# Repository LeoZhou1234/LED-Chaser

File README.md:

# LED Chaser #
Made by following the tutorial from Hack Club Blueprint.  
Gerbers were generated matching JLCPCB guidelines.

## Schematic ##

## PCB ##

(Snoopy silkscreen omitted for clarity)

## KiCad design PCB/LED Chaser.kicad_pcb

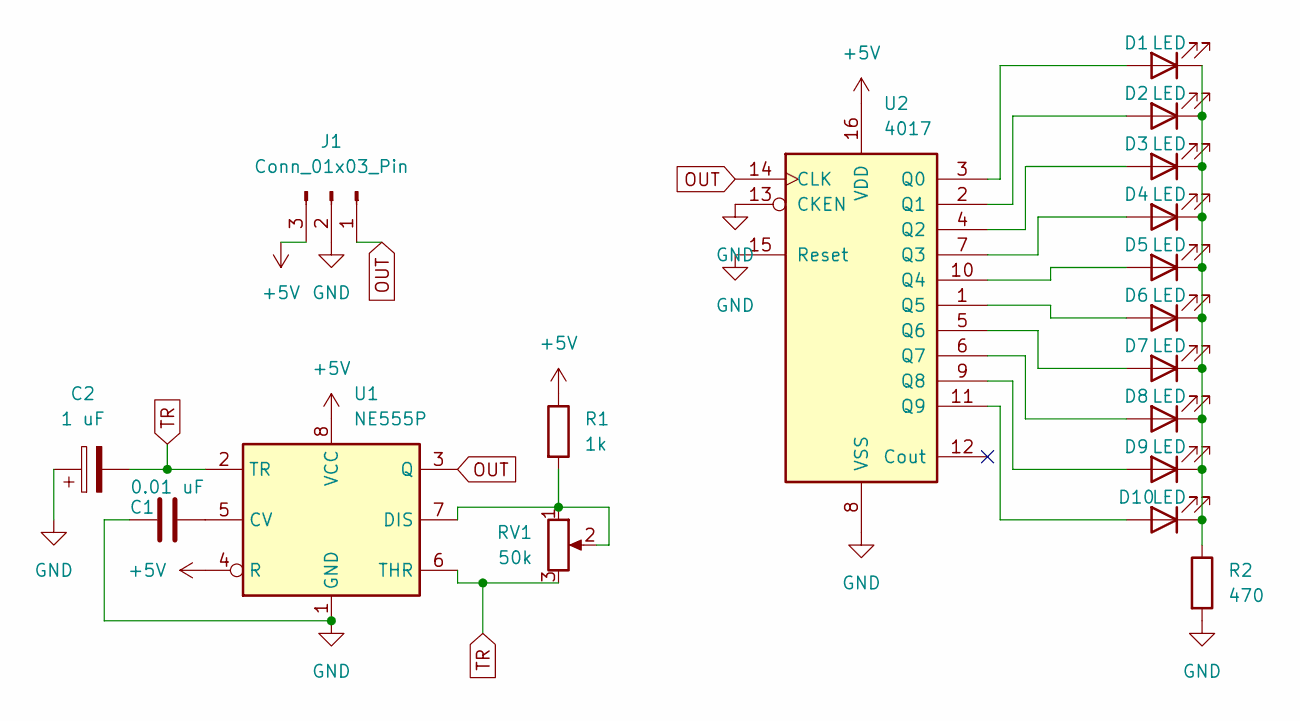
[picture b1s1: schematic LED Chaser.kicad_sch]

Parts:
C1: 0.01 uF; CP_Radial_D5.0mm_P2.00mm
C2: 1 uF; CP_Radial_D5.0mm_P2.00mm
D1, D2, D3, D4, D5, D6, D7, D8, D9, D10: LED; LED_D3.0mm
J1: Conn_01x03_Pin; PinHeader_1x03_P2.54mm_Vertical
R1: 1k; R_Axial_DIN0207_L6.3mm_D2.5mm_P10.16mm_Horizontal
R2: 470; R_Axial_DIN0207_L6.3mm_D2.5mm_P10.16mm_Horizontal
RV1: 50k; Potentiometer_Bourns_3296X_Horizontal
U1: NE555P; DIP-8_W7.62mm
U2: 4017; N16

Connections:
+5V: J1.3, R1.1, U1.4 (R), U1.8 (VCC), U2.16 (VDD)
GND: C1.1, C2.1, J1.2, R2.2, U1.1 (GND), U2.8 (VSS), U2.13 (CKEN), U2.15 (Reset)
unnamed: D1.2 (A), U2.3 (Q0)
unnamed: D1.1 (K), D2.1 (K), D3.1 (K), D4.1 (K), D5.1 (K), D6.1 (K), D7.1 (K), D8.1 (K), D9.1 (K), D10.1 (K), R2.1
unnamed: D2.2 (A), U2.2 (Q1)
unnamed: D3.2 (A), U2.4 (Q2)
unnamed: D4.2 (A), U2.7 (Q3)
unnamed: D5.2 (A), U2.10 (Q4)
unnamed: D6.2 (A), U2.1 (Q5)
unnamed: D7.2 (A), U2.5 (Q6)
unnamed: D8.2 (A), U2.6 (Q7)
unnamed: D9.2 (A), U2.9 (Q8)
unnamed: D10.2 (A), U2.11 (Q9)
unnamed: C1.2, U1.5 (CV)
unnamed: R1.2, RV1.1, RV1.2, U1.7 (DIS)
OUT: J1.1, U1.3 (Q), U2.14 (CLK)
TR: C2.2, RV1.3, U1.2 (TR), U1.6 (THR)

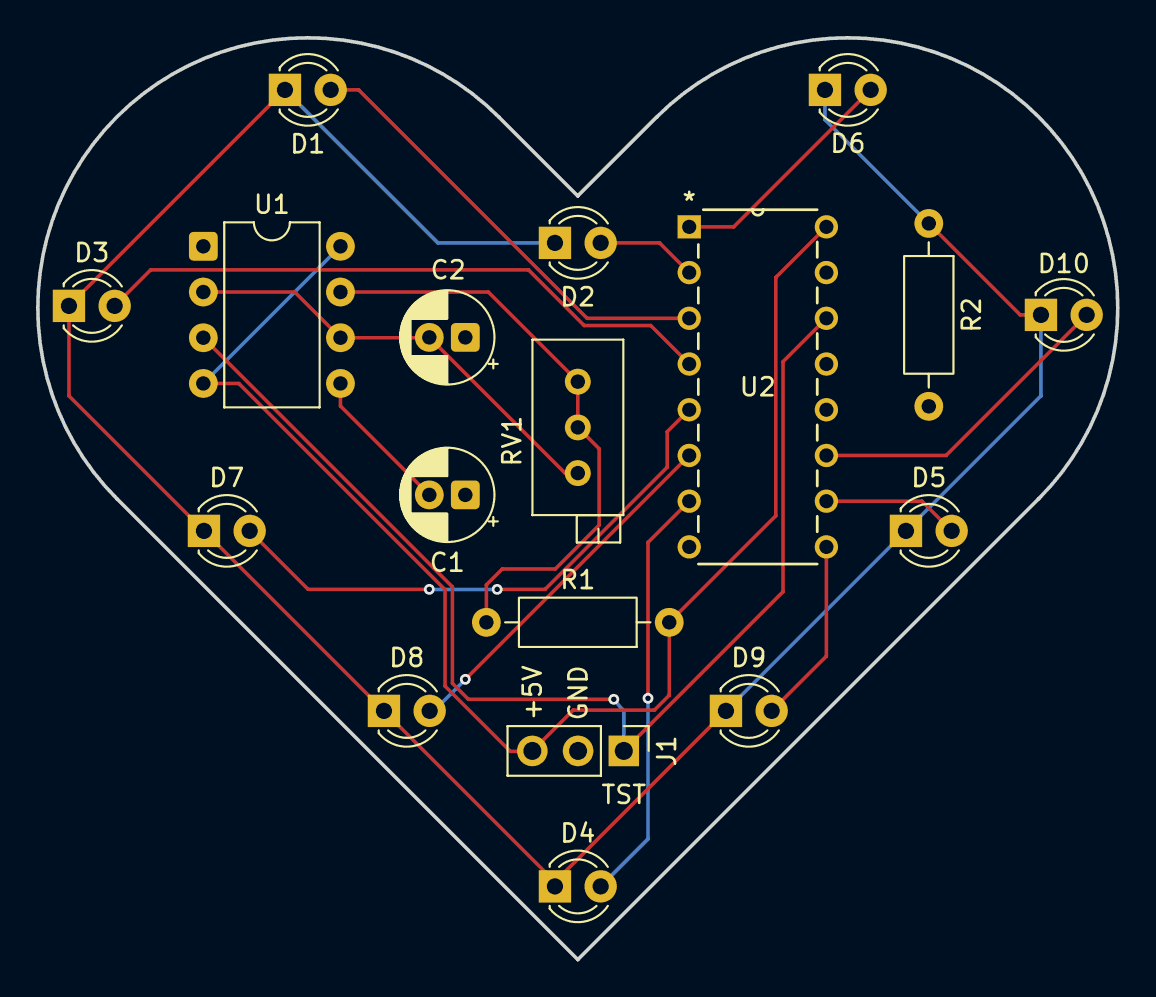
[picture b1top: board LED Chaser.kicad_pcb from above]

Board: 2 copper layers, 60.0 x 51.2 mm, 18 parts (0 on the bottom side), 17 nets.

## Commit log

2025-12-26 modified back silkscreen
2025-12-27 cleaned up schematic and updated readme
